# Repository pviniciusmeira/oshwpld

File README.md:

# OSHW with Programmable Logic Device
Project of a Development board to work with reconfigurable logic.

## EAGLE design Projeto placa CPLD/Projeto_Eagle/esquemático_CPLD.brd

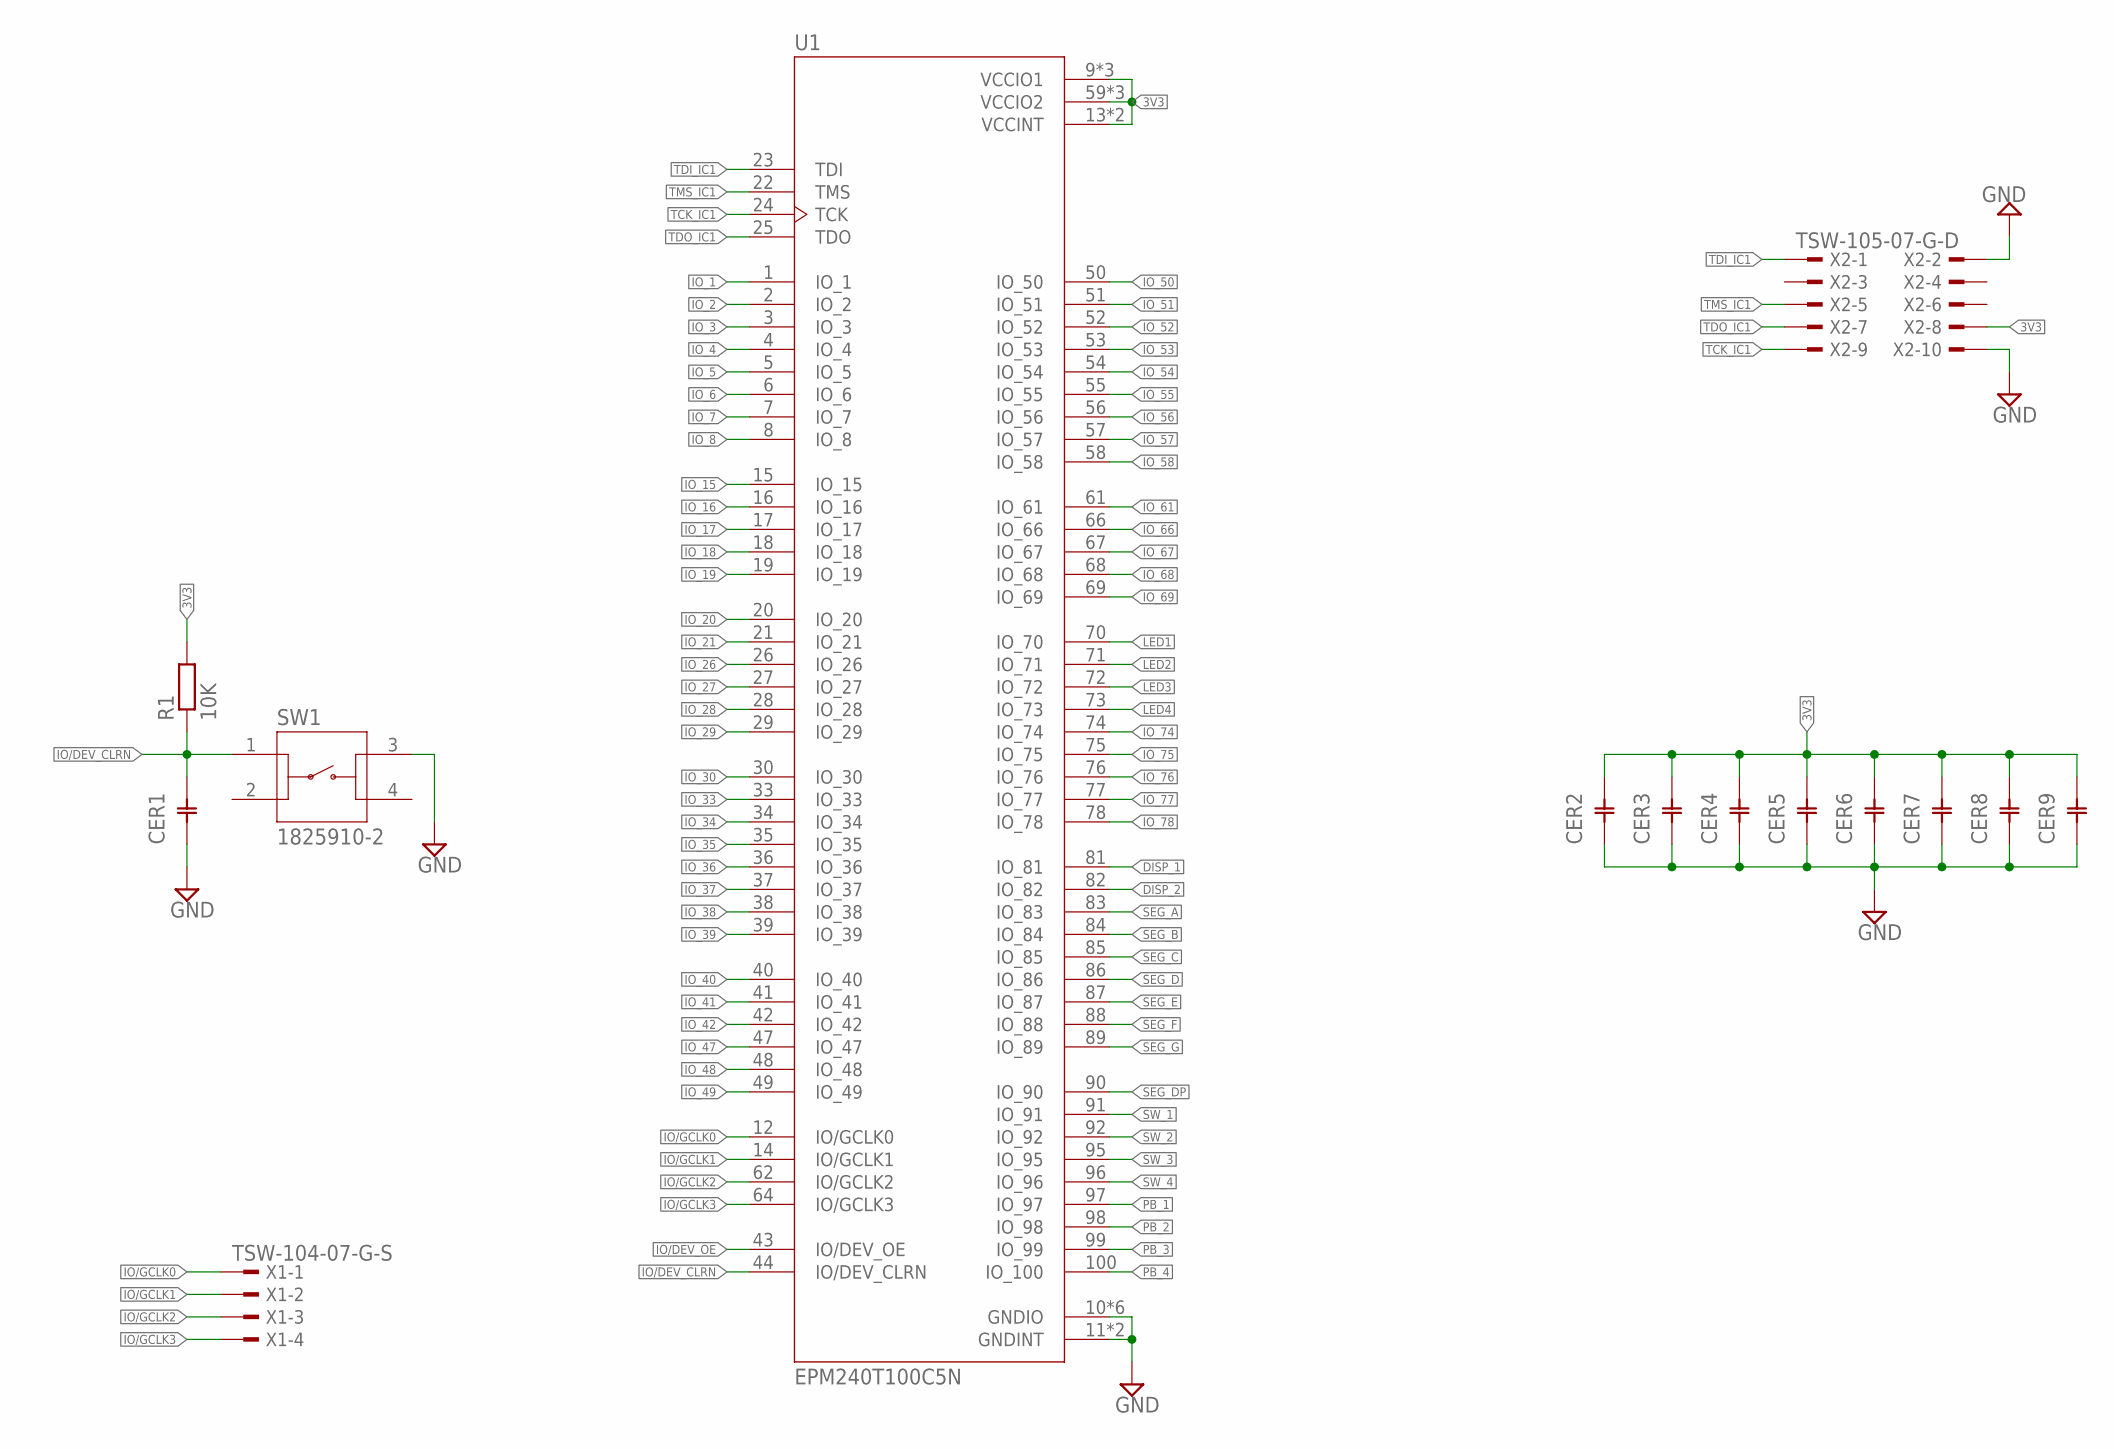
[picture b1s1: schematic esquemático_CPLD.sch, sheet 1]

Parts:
CER1, CER2, CER3, CER4, CER5, CER6, CER7, CER8, CER9: 100nF; CERACAPA
R1: 10K; 0204/7
SW1: 1825910-2; TE_1825910-2
U1: EPM240T100C5N; QFP50P1600X1600X120-100N
X1: TSW-104-07-G-S; TSW-104-XX-G-S
X2: TSW-105-07-G-D; TSW-105-XX-G-D

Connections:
3V3: CER2.P$2, CER3.P$2, CER4.P$2, CER5.P$2, CER6.P$2, CER7.P$2, CER8.P$2, CER9.P$2, R1.2, U1.9 (VCCIO1), U1.13 (VCCINT), U1.31 (VCCIO1), U1.45 (VCCIO1), U1.59 (VCCIO2), U1.63 (VCCINT), U1.80 (VCCIO2), U1.94 (VCCIO2), X2.8; also elsewhere on the board
DISP_1: U1.81 (IO_81); also elsewhere on the board
DISP_2: U1.82 (IO_82); also elsewhere on the board
GND: CER1.P$1, CER2.P$1, CER3.P$1, CER4.P$1, CER5.P$1, CER6.P$1, CER7.P$1, CER8.P$1, CER9.P$1, SW1.3, U1.10 (GNDIO), U1.11 (GNDINT), U1.32 (GNDIO), U1.46 (GNDIO), U1.60 (GNDIO), U1.65 (GNDINT), U1.79 (GNDIO), U1.93 (GNDIO), X2.2, X2.10; also elsewhere on the board
IO/DEV_CLRN: CER1.P$2, R1.1, SW1.1, U1.44 (IO/DEV_CLRN)
IO/DEV_OE: U1.43 (IO/DEV_OE); also elsewhere on the board
IO/GCLK0: U1.12 (IO/GCLK0), X1.1
IO/GCLK1: U1.14 (IO/GCLK1), X1.2
IO/GCLK2: U1.62 (IO/GCLK2), X1.3
IO/GCLK3: U1.64 (IO/GCLK3), X1.4
IO_1: U1.1 (IO_1); also elsewhere on the board
IO_2: U1.2 (IO_2); also elsewhere on the board
IO_3: U1.3 (IO_3); also elsewhere on the board
IO_4: U1.4 (IO_4); also elsewhere on the board
IO_5: U1.5 (IO_5); also elsewhere on the board
IO_6: U1.6 (IO_6); also elsewhere on the board
IO_7: U1.7 (IO_7); also elsewhere on the board
IO_8: U1.8 (IO_8); also elsewhere on the board
IO_15: U1.15 (IO_15); also elsewhere on the board
IO_16: U1.16 (IO_16); also elsewhere on the board
IO_17: U1.17 (IO_17); also elsewhere on the board
IO_18: U1.18 (IO_18); also elsewhere on the board
IO_19: U1.19 (IO_19); also elsewhere on the board
IO_20: U1.20 (IO_20); also elsewhere on the board
IO_21: U1.21 (IO_21); also elsewhere on the board
IO_26: U1.26 (IO_26); also elsewhere on the board
IO_27: U1.27 (IO_27); also elsewhere on the board
IO_28: U1.28 (IO_28); also elsewhere on the board
IO_29: U1.29 (IO_29); also elsewhere on the board
IO_30: U1.30 (IO_30); also elsewhere on the board
IO_33: U1.33 (IO_33); also elsewhere on the board
IO_34: U1.34 (IO_34); also elsewhere on the board
IO_35: U1.35 (IO_35); also elsewhere on the board
IO_36: U1.36 (IO_36); also elsewhere on the board
IO_37: U1.37 (IO_37); also elsewhere on the board
IO_38: U1.38 (IO_38); also elsewhere on the board
IO_39: U1.39 (IO_39); also elsewhere on the board
IO_40: U1.40 (IO_40); also elsewhere on the board
IO_41: U1.41 (IO_41); also elsewhere on the board
IO_42: U1.42 (IO_42); also elsewhere on the board
IO_47: U1.47 (IO_47); also elsewhere on the board
IO_48: U1.48 (IO_48); also elsewhere on the board
IO_49: U1.49 (IO_49); also elsewhere on the board
IO_50: U1.50 (IO_50); also elsewhere on the board
IO_51: U1.51 (IO_51); also elsewhere on the board
IO_52: U1.52 (IO_52); also elsewhere on the board
IO_53: U1.53 (IO_53); also elsewhere on the board
IO_54: U1.54 (IO_54); also elsewhere on the board
IO_55: U1.55 (IO_55); also elsewhere on the board
IO_56: U1.56 (IO_56); also elsewhere on the board
IO_57: U1.57 (IO_57); also elsewhere on the board
IO_58: U1.58 (IO_58); also elsewhere on the board
IO_61: U1.61 (IO_61); also elsewhere on the board
IO_66: U1.66 (IO_66); also elsewhere on the board
IO_67: U1.67 (IO_67); also elsewhere on the board
IO_68: U1.68 (IO_68); also elsewhere on the board
IO_69: U1.69 (IO_69); also elsewhere on the board
IO_74: U1.74 (IO_74); also elsewhere on the board
IO_75: U1.75 (IO_75); also elsewhere on the board
IO_76: U1.76 (IO_76); also elsewhere on the board
IO_77: U1.77 (IO_77); also elsewhere on the board
IO_78: U1.78 (IO_78); also elsewhere on the board
LED1: U1.70 (IO_70); also elsewhere on the board
LED2: U1.71 (IO_71); also elsewhere on the board
LED3: U1.72 (IO_72); also elsewhere on the board
LED4: U1.73 (IO_73); also elsewhere on the board
PB_1: U1.97 (IO_97); also elsewhere on the board
PB_2: U1.98 (IO_98); also elsewhere on the board
PB_3: U1.99 (IO_99); also elsewhere on the board
PB_4: U1.100 (IO_100); also elsewhere on the board
SEG_A: U1.83 (IO_83); also elsewhere on the board
SEG_B: U1.84 (IO_84); also elsewhere on the board
SEG_C: U1.85 (IO_85); also elsewhere on the board
SEG_D: U1.86 (IO_86); also elsewhere on the board
SEG_DP: U1.90 (IO_90); also elsewhere on the board
SEG_E: U1.87 (IO_87); also elsewhere on the board
SEG_F: U1.88 (IO_88); also elsewhere on the board
SEG_G: U1.89 (IO_89); also elsewhere on the board
SW_1: U1.91 (IO_91); also elsewhere on the board
SW_2: U1.92 (IO_92); also elsewhere on the board
SW_3: U1.95 (IO_95); also elsewhere on the board
SW_4: U1.96 (IO_96); also elsewhere on the board
TCK_IC1: U1.24 (TCK), X2.9
TDI_IC1: U1.23 (TDI), X2.1
TDO_IC1: U1.25 (TDO), X2.7
TMS_IC1: U1.22 (TMS), X2.5

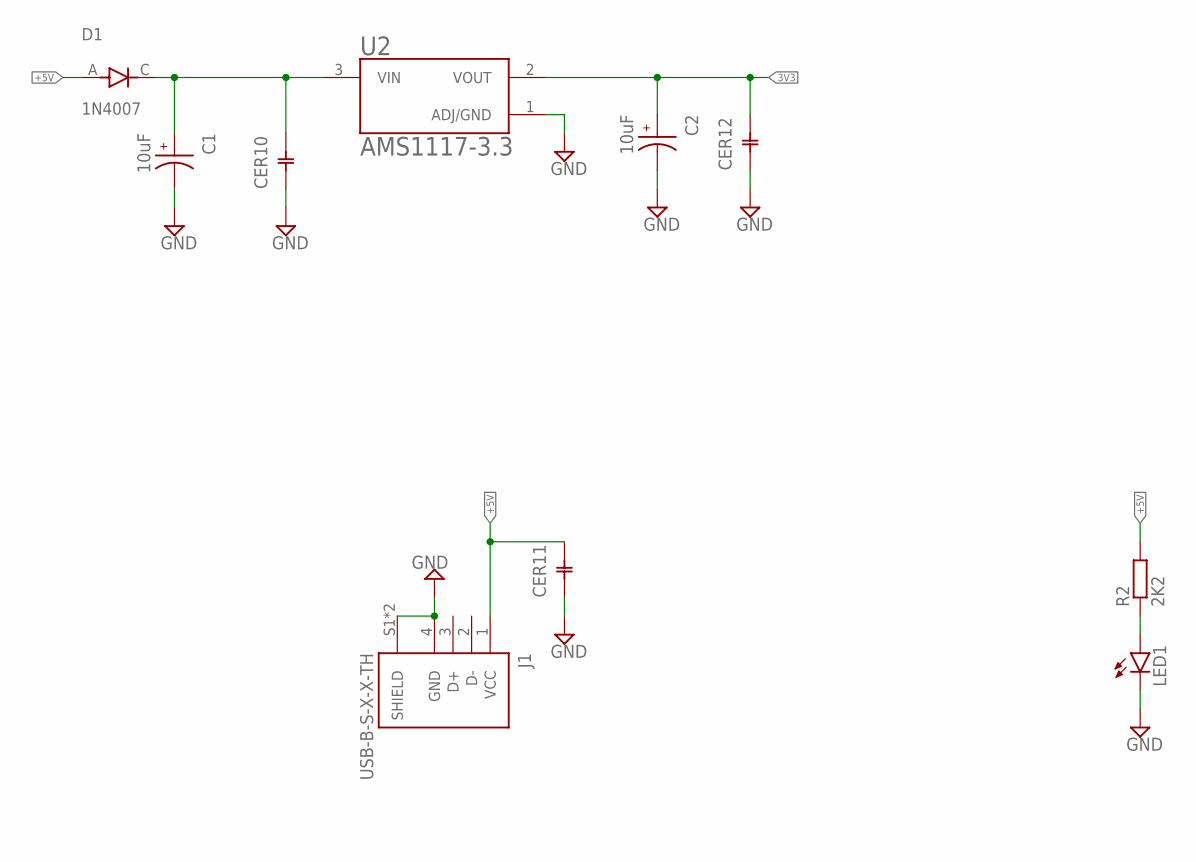
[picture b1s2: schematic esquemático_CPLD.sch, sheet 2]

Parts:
C1, C2: 10uF; CAPPRD150W45D400H700
CER10, CER11, CER12: 100nF; CERACAPA
D1: 1N4007; DIOAD1060W80L520D270
J1: USB-B-S-X-X-TH; SAMTEC_USB-B-S-X-X-TH
LED1: LED5MM
R2: 2K2; 0204/7
U2: AMS1117-3.3; SOT229P700X180-4N

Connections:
3V3: C2.P, CER12.P$2, U2.2 (VOUT); also elsewhere on the board
+5V: CER11.P$2, D1.A, J1.1 (VCC), R2.2
GND: C1.N, C2.N, CER10.P$1, CER11.P$1, CER12.P$1, J1.4 (GND), J1.S1 (SHIELD), J1.S2 (SHIELD), LED1.K (C), U2.1 (ADJ/GND); also elsewhere on the board
unnamed: LED1.A, R2.1
unnamed: C1.P, CER10.P$2, D1.C, U2.3 (VIN)

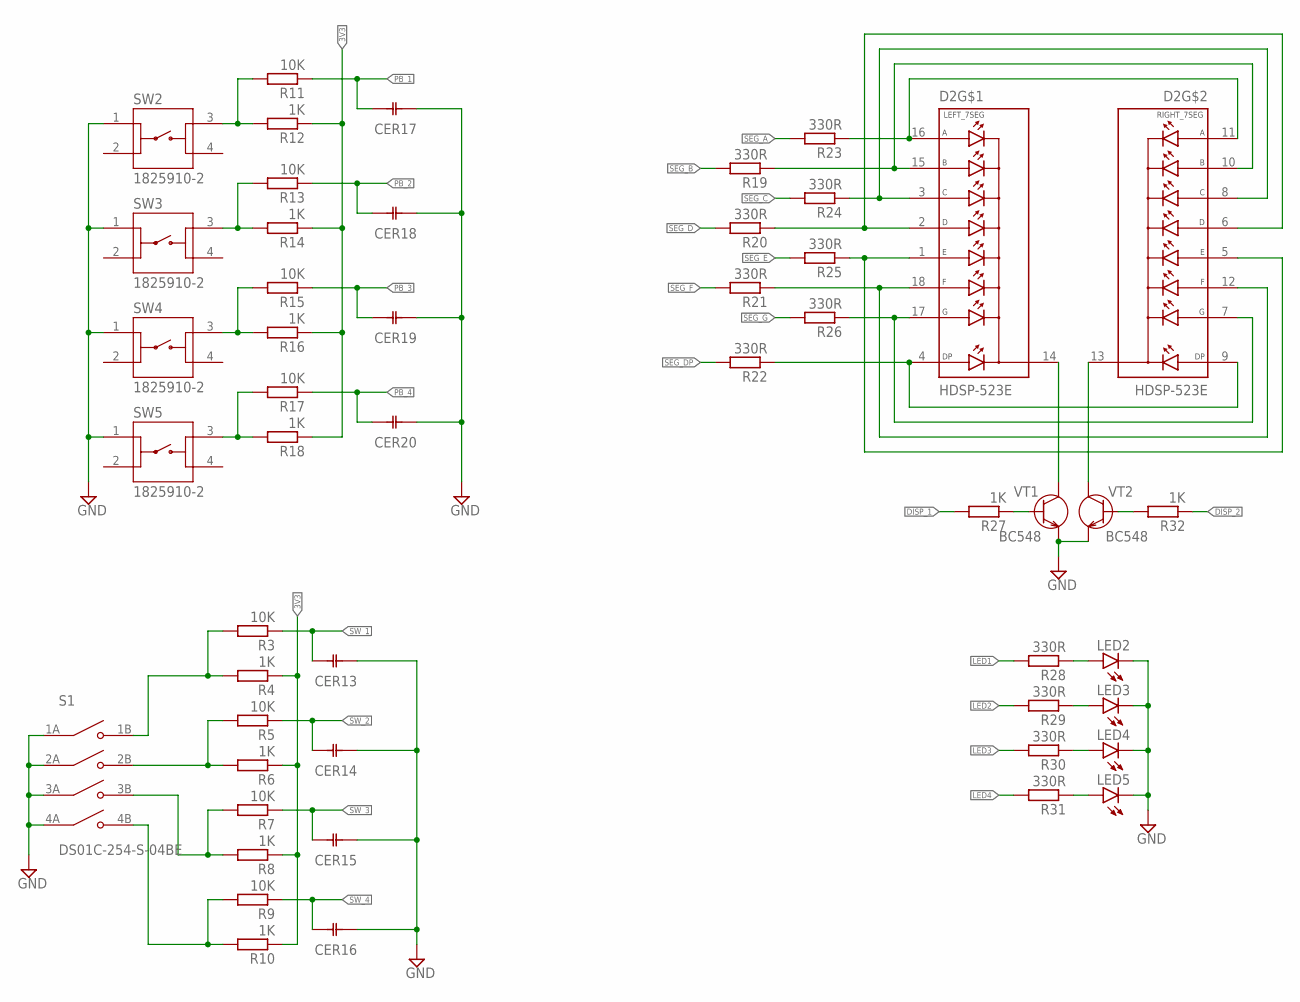
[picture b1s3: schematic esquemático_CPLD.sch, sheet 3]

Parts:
CER13, CER14, CER15, CER16, CER17, CER18, CER19, CER20: 100nF; CERACAPA
D2: HDSP-523E; LED_HDSP-523E
LED2, LED3, LED4, LED5: LED5MM
R3, R5, R7, R9, R11, R13, R15, R17: 10K; 0204/7
R4, R6, R8, R10, R12, R14, R16, R18, R27, R32: 1K; 0204/7
R19, R20, R21, R22, R23, R24, R25, R26, R28, R29, R30, R31: 330R; 0204/7
S1: DS01C-254-S-04BE; SW_DS01C-254-S-04BE
SW2, SW3, SW4, SW5: 1825910-2; TE_1825910-2
VT1, VT2: BC548; TO92

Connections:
3V3: R4.1, R6.1, R8.1, R10.1, R12.1, R14.1, R16.1, R18.1; also elsewhere on the board
DISP_1: R27.2; also elsewhere on the board
DISP_2: R32.1; also elsewhere on the board
GND: CER13.P$1, CER14.P$1, CER15.P$1, CER16.P$1, CER17.P$1, CER18.P$1, CER19.P$1, CER20.P$1, LED2.K (C), LED3.K (C), LED4.K (C), LED5.K (C), S1.1A (COM1), S1.2A (COM2), S1.3A (COM3), S1.4A (COM4), SW2.1, SW3.1, SW4.1, SW5.1, VT1.E, VT2.E; also elsewhere on the board
LED1: R28.2; also elsewhere on the board
LED2: R29.2; also elsewhere on the board
LED3: R30.2; also elsewhere on the board
LED4: R31.2; also elsewhere on the board
unnamed: R11.2, R12.2, SW2.3
unnamed: R3.2, R4.2, S1.1B (NO1)
unnamed: R5.2, R6.2, S1.2B (NO2)
unnamed: R9.2, R10.2, S1.4B (NO4)
unnamed: R7.2, R8.2, S1.3B (NO3)
unnamed: R13.2, R14.2, SW3.3
unnamed: R15.2, R16.2, SW4.3
unnamed: R17.2, R18.2, SW5.3
unnamed: D2.11 (A_2), D2.16 (A_1), R23.1
unnamed: D2.10 (B_2), D2.15 (B_1), R19.1
unnamed: D2.3 (C_1), D2.8 (C_2), R24.1
unnamed: D2.2 (D_1), D2.6 (D_2), R20.1
unnamed: D2.4 (DP_1), D2.9 (DP_2), R22.1
unnamed: D2.7 (G_2), D2.17 (G_1), R26.1
unnamed: D2.12 (F_2), D2.18 (F_1), R21.1
unnamed: D2.1 (E_1), D2.5 (E_2), R25.1
unnamed: D2.13 (COM_2), VT2.C
unnamed: D2.14 (COM_1), VT1.C
unnamed: R27.1, VT1.B
unnamed: R32.2, VT2.B
unnamed: LED2.A, R28.1
unnamed: LED3.A, R29.1
unnamed: LED4.A, R30.1
unnamed: LED5.A, R31.1
PB_1: CER17.P$2, R11.1; also elsewhere on the board
PB_2: CER18.P$2, R13.1; also elsewhere on the board
PB_3: CER19.P$2, R15.1; also elsewhere on the board
PB_4: CER20.P$2, R17.1; also elsewhere on the board
SEG_A: R23.2; also elsewhere on the board
SEG_B: R19.2; also elsewhere on the board
SEG_C: R24.2; also elsewhere on the board
SEG_D: R20.2; also elsewhere on the board
SEG_DP: R22.2; also elsewhere on the board
SEG_E: R25.2; also elsewhere on the board
SEG_F: R21.2; also elsewhere on the board
SEG_G: R26.2; also elsewhere on the board
SW_1: CER13.P$2, R3.1; also elsewhere on the board
SW_2: CER14.P$2, R5.1; also elsewhere on the board
SW_3: CER15.P$2, R7.1; also elsewhere on the board
SW_4: CER16.P$2, R9.1; also elsewhere on the board

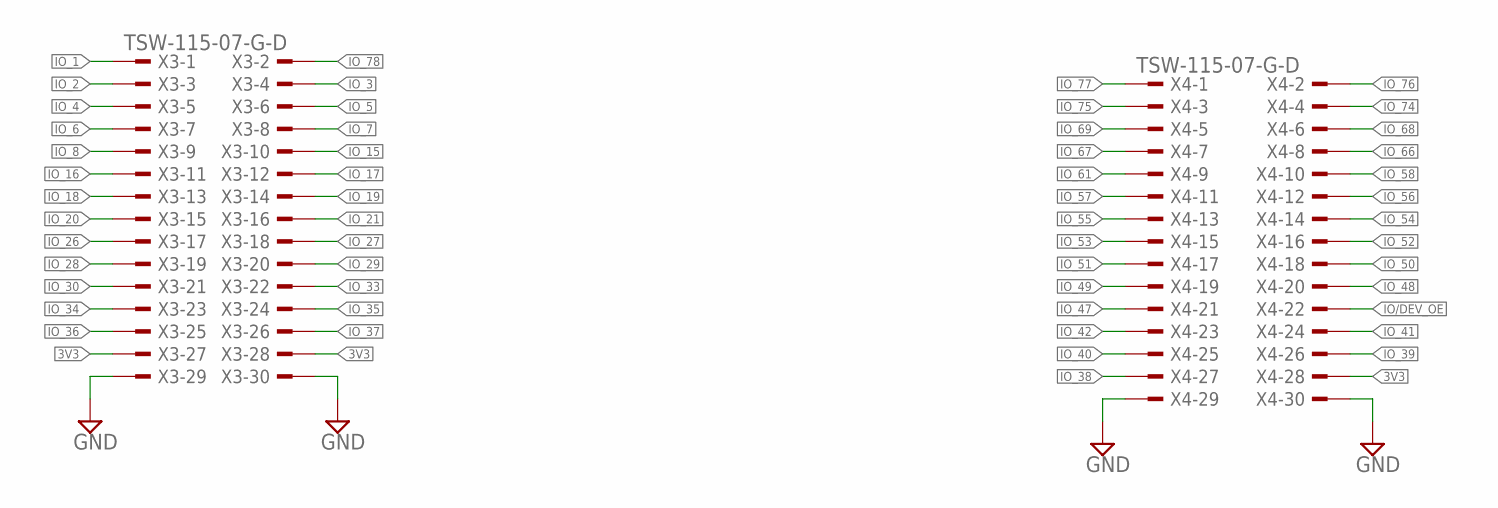
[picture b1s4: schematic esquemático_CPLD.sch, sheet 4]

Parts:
X3, X4: TSW-115-07-G-D; TSW-115-XX-G-D

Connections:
3V3: X3.27, X3.28, X4.28; also elsewhere on the board
GND: X3.29, X3.30, X4.29, X4.30; also elsewhere on the board
IO/DEV_OE: X4.22; also elsewhere on the board
IO_1: X3.1; also elsewhere on the board
IO_2: X3.3; also elsewhere on the board
IO_3: X3.4; also elsewhere on the board
IO_4: X3.5; also elsewhere on the board
IO_5: X3.6; also elsewhere on the board
IO_6: X3.7; also elsewhere on the board
IO_7: X3.8; also elsewhere on the board
IO_8: X3.9; also elsewhere on the board
IO_15: X3.10; also elsewhere on the board
IO_16: X3.11; also elsewhere on the board
IO_17: X3.12; also elsewhere on the board
IO_18: X3.13; also elsewhere on the board
IO_19: X3.14; also elsewhere on the board
IO_20: X3.15; also elsewhere on the board
IO_21: X3.16; also elsewhere on the board
IO_26: X3.17; also elsewhere on the board
IO_27: X3.18; also elsewhere on the board
IO_28: X3.19; also elsewhere on the board
IO_29: X3.20; also elsewhere on the board
IO_30: X3.21; also elsewhere on the board
IO_33: X3.22; also elsewhere on the board
IO_34: X3.23; also elsewhere on the board
IO_35: X3.24; also elsewhere on the board
IO_36: X3.25; also elsewhere on the board
IO_37: X3.26; also elsewhere on the board
IO_38: X4.27; also elsewhere on the board
IO_39: X4.26; also elsewhere on the board
IO_40: X4.25; also elsewhere on the board
IO_41: X4.24; also elsewhere on the board
IO_42: X4.23; also elsewhere on the board
IO_47: X4.21; also elsewhere on the board
IO_48: X4.20; also elsewhere on the board
IO_49: X4.19; also elsewhere on the board
IO_50: X4.18; also elsewhere on the board
IO_51: X4.17; also elsewhere on the board
IO_52: X4.16; also elsewhere on the board
IO_53: X4.15; also elsewhere on the board
IO_54: X4.14; also elsewhere on the board
IO_55: X4.13; also elsewhere on the board
IO_56: X4.12; also elsewhere on the board
IO_57: X4.11; also elsewhere on the board
IO_58: X4.10; also elsewhere on the board
IO_61: X4.9; also elsewhere on the board
IO_66: X4.8; also elsewhere on the board
IO_67: X4.7; also elsewhere on the board
IO_68: X4.6; also elsewhere on the board
IO_69: X4.5; also elsewhere on the board
IO_74: X4.4; also elsewhere on the board
IO_75: X4.3; also elsewhere on the board
IO_76: X4.2; also elsewhere on the board
IO_77: X4.1; also elsewhere on the board
IO_78: X3.2; also elsewhere on the board

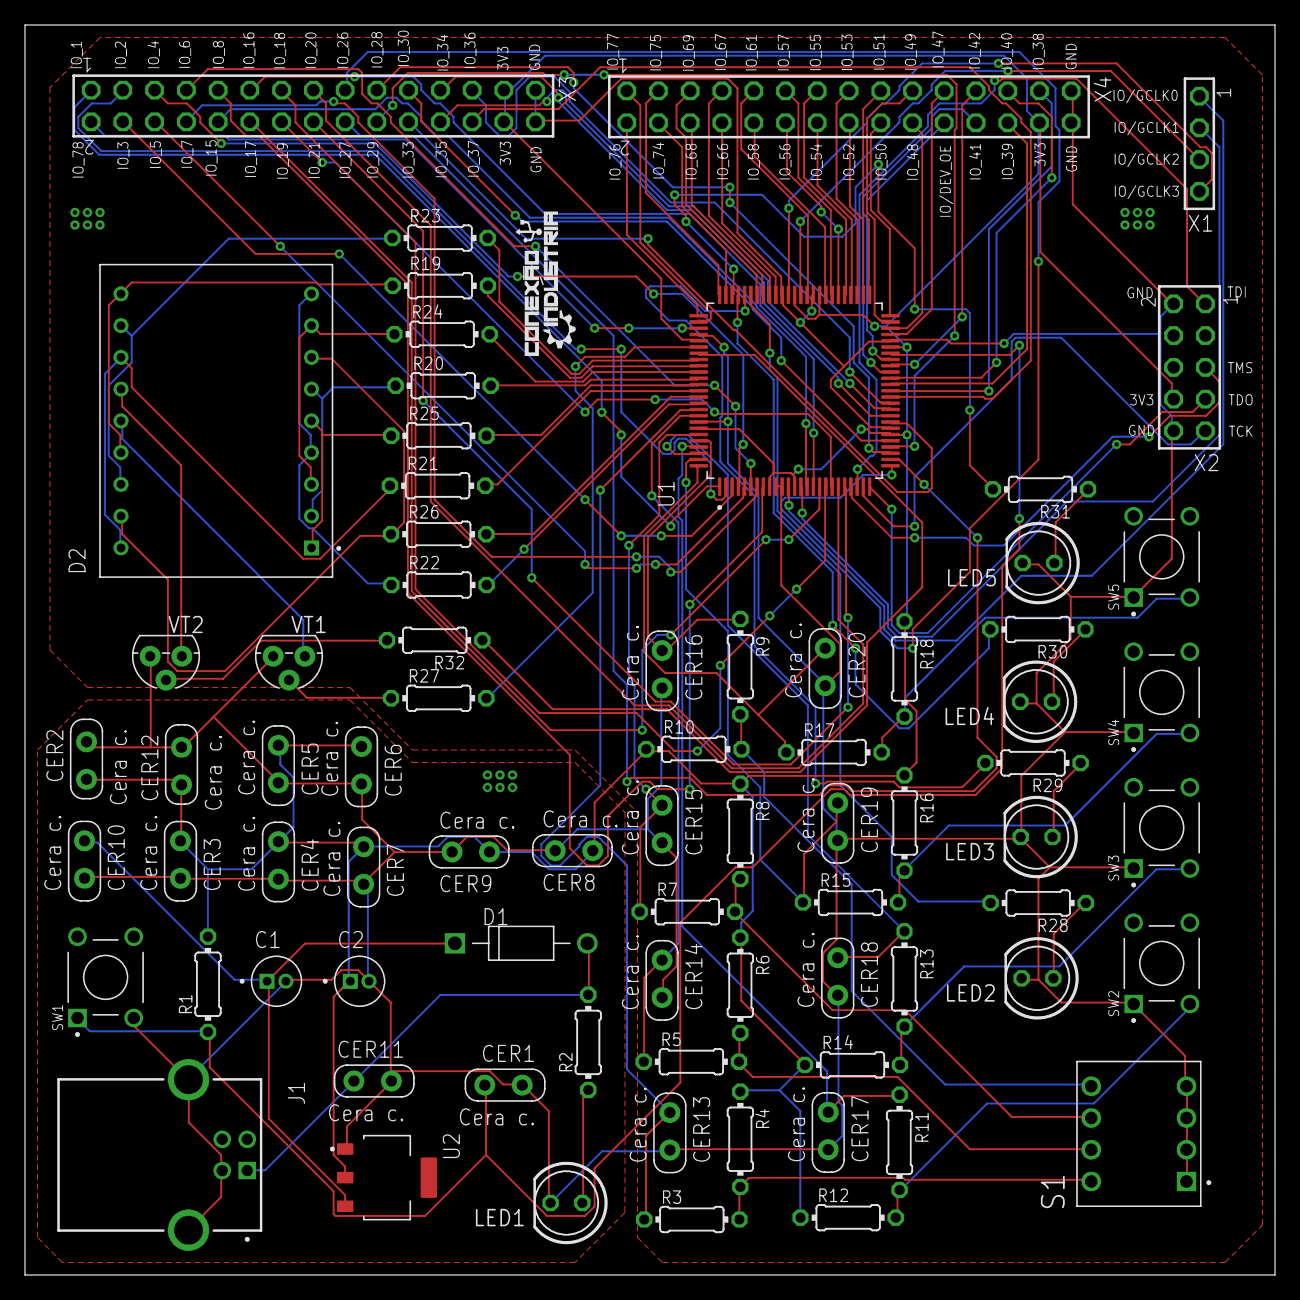
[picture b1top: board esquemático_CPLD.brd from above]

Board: 2 copper layers, 100.0 x 100.0 mm, 76 parts (0 on the bottom side), 113 nets.

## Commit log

2022-11-18 Arquivos para elaboração da placa
2022-11-18 Licença do projeto
